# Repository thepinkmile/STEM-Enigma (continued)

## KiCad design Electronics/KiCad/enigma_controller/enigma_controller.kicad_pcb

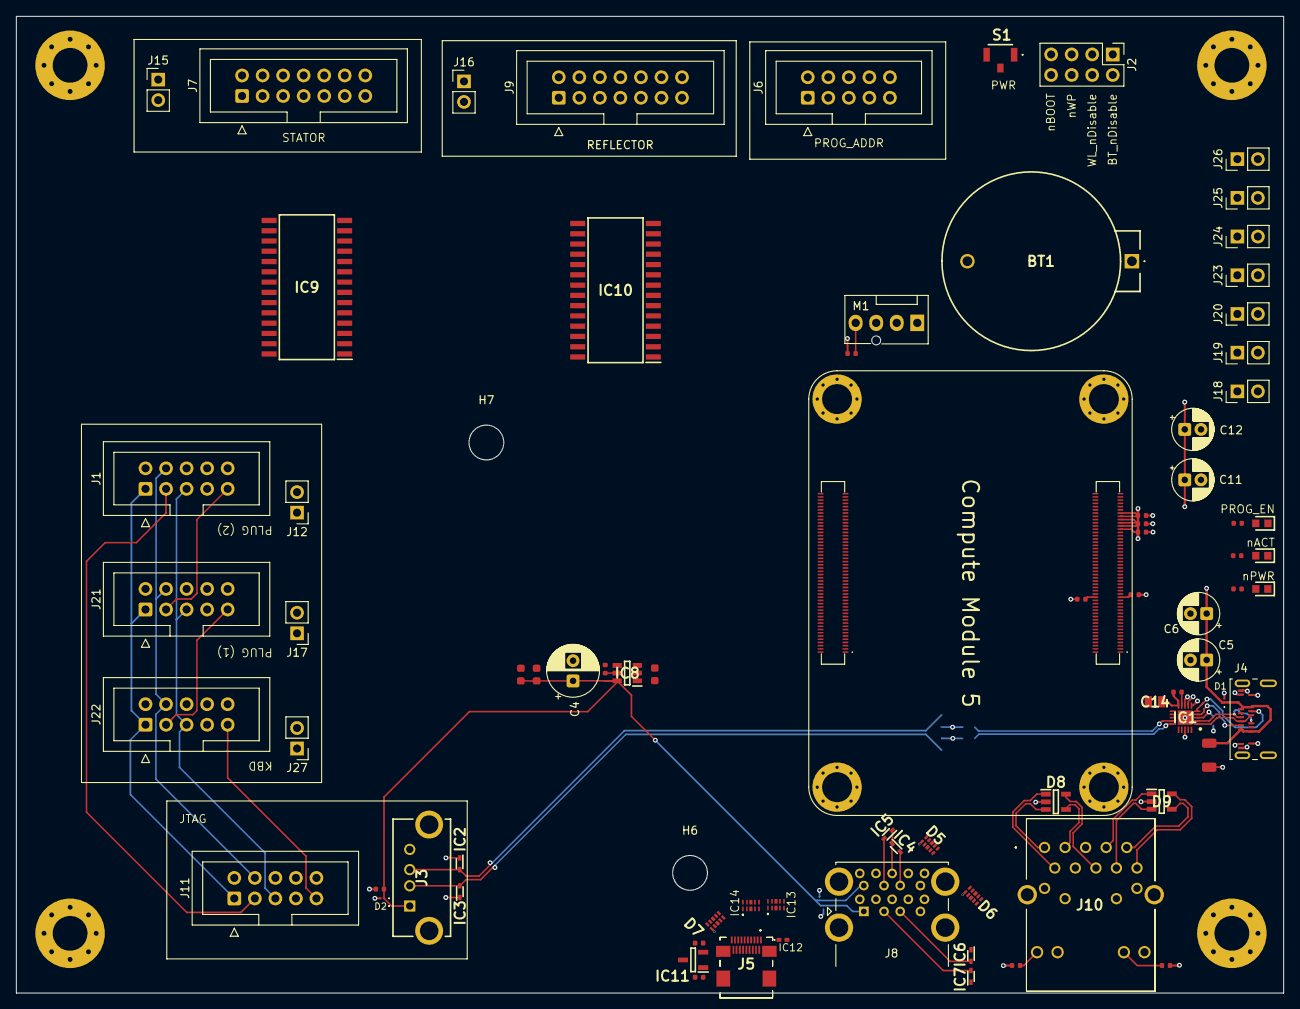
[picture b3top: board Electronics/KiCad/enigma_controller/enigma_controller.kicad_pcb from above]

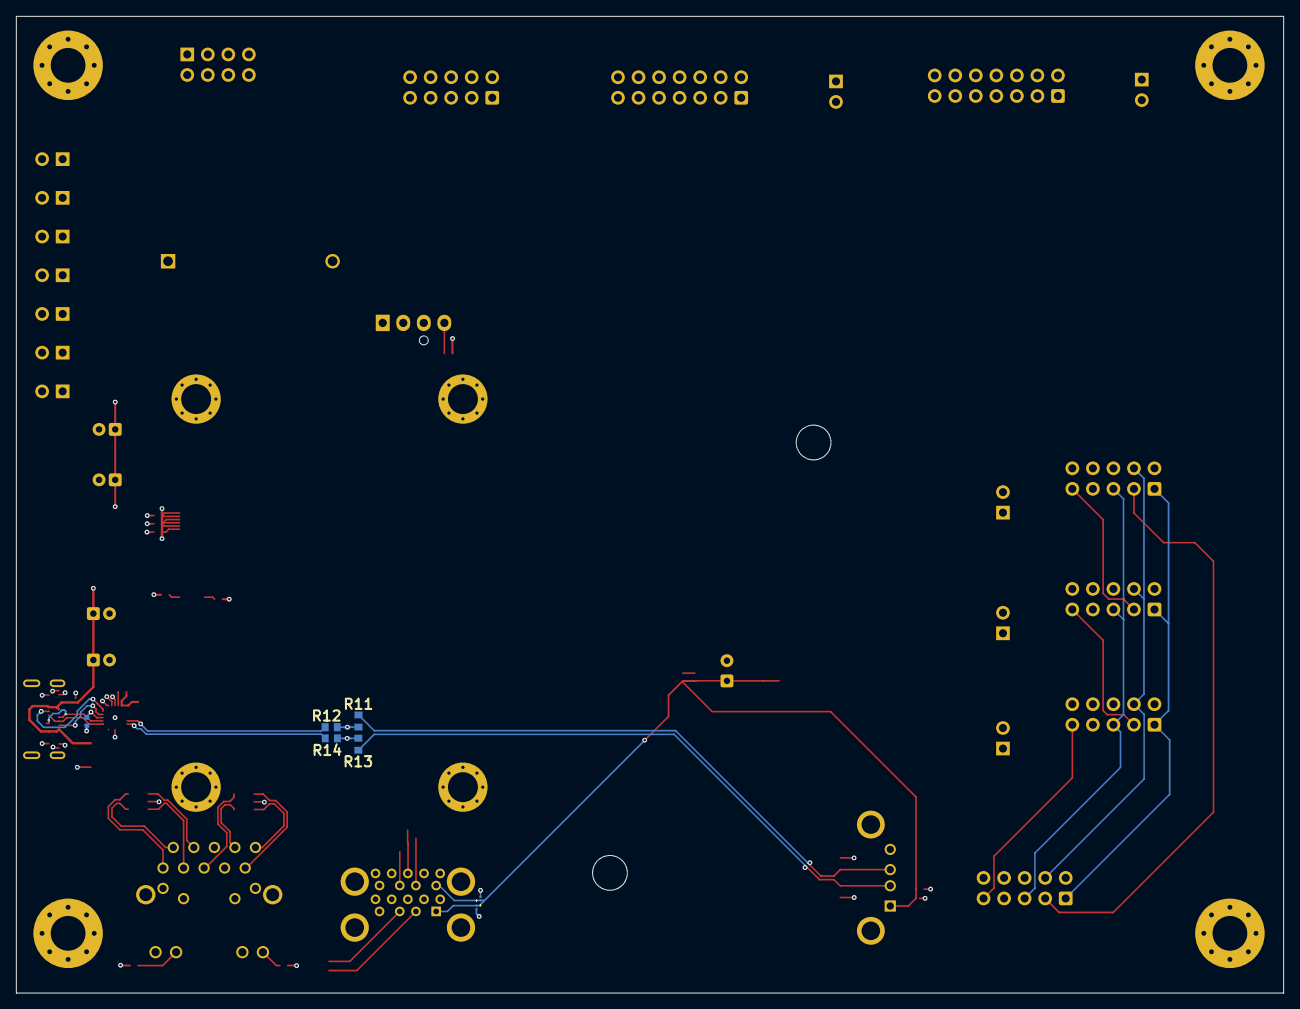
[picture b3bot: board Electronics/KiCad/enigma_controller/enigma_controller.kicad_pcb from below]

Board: 6 copper layers, 156.7 x 120.8 mm, 92 parts (7 on the bottom side), 135 nets.

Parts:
BT1: BS-02-A1AJ006; BS02A1AJ006
C1, C2, C7, C8, C9, C15, C16: 100nF; C_0402
C3, C18, C19: 10uF; C_0603
C4: 100uF_25V; CP_Radial_D6.3mm_P2.50mm
C5, C6, C11, C12: 4.7uF 50V; CP_Radial_D5.0mm_P2.00mm
C13: 2.2uF; C_1206
C14: CL21B105KAFNNNG; CAPC2012X135N
D1, D2, D3, D4: ESD441DPLR
D5, D6: TPD4E02B04DQAR; DQA(R-PUSON-N10)
D7: TPD4E05U06DQAR; DQA(R-PUSON-N10)
D8, D9: ESDS314DBVR; SOT95P280X145-5N
H1: RaspberryPi-CM5-Carrier-Tall-Pad-Via-Standoff
H2, H3, H4, H5: MountingHole_Pad; MountingHole_4.3mm_M4_Pad_Via
H6, H7: MountingHole; MountingHole_4.3mm_M4
IC1: TPD8S300ARUKR; QFN40P300X300X80-21N-D
IC2, IC3, IC4, IC5, IC6, IC7: ESD321DYAR; SODFL1608X77N
IC8: AP22653W6-7; SOT95P280X145-6N
IC9, IC10: MCP23017-E_SO; SOIC127P1030X265-28N
IC11: RT9742SNGV; SOT95P279X130-3N
IC12: TPD1E05U06DPYT
IC13, IC14: ESD224DQAR
J1, J6, J11, J21, J22: Conn_02x05_Odd_Even; IDC-Header_2x05_P2.54mm_Vertical
J2: Conn_02x04_Odd_Even; PinHeader_2x04_P2.54mm_Vertical
J3: USB1040-GF-L-B; USB1040GFLB
J4: USB_C_Receptacle_USB2.0_16P; USB_C_Receptacle_Amphenol_124019772112A
J5: 46765-0301; 467650301
J7, J9: Conn_02x07_Odd_Even; IDC-Header_2x07_P2.54mm_Vertical
J8: USB3_A_Stacked; USB3_A_Molex_48406-0001_Horizontal_Stacked
J10: A70-112-331N126; A70112331N126
J12, J15, J16, J17, J18, J19, J20, J23, J24, J25, J26, J27: Conn_01x02; PinHeader_1x02_P2.54mm_Vertical
LED1, LED2, LED87: KT-0603R; LEDC1608X70N
M1: Fan_4pin; FanPinHeader_1x04_P2.54mm_Vertical
R1, R2, R3, R4: 470Ω; R_0402
R5: 100kΩ; R_0402
R6, R7: 2.2kΩ; R_0402
R8: 10kΩ; R_0402
R9: 15kΩ; R_0402
R10: 1kΩ; R_0402
R11, R12, R13, R14: RCA06030000ZSEA; RESC1608X50N
S1: B3U-1100PM; B3U1100PM

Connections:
+3V3: C11.1, C12.1, C14.2, C15.1, H1.78 (GPIO_VREF), H1.84 (CM5_3.3V_(Output)), H1.86 (CM5_3.3V_(Output)), IC1.10 (VPWR), IC9.9 (VDD), IC10.9 (VDD), IC10.15 (A0), J12.1, J15.1, J16.1, J17.1, J18.1, J19.1, J20.1, J23.1, J24.1, J25.1, J26.1, J27.1, R1.2, R2.2, R3.2, R4.2, R5.1, R6.2, R7.1, R8.1
+5V: C1.1, C2.1, C5.1, C6.1, C7.1, C9.1, C13.1, C18.1, D1.1, H1.77 (+5V_(Input)), H1.79 (+5V_(Input)), H1.81 (+5V_(Input)), H1.83 (+5V_(Input)), H1.85 (+5V_(Input)), H1.87 (+5V_(Input)), IC8.1 (IN), IC11.1 (VIN), J4.A4 (VBUS), J4.A9 (VBUS), J4.B4 (VBUS), J4.B9 (VBUS), M1.2 (+)
/BT_nDisable: H1.91 (BT_nDisable), J2.2
/C_CC1: IC1.4 (C_CC1), J4.A5 (CC1)
/C_CC2: IC1.5 (C_CC2), J4.B5 (CC2)
/C_D+: IC1.1 (C_SBU1), J4.A6 (D+), J4.B6 (D+)
/C_D-: IC1.2 (C_SBU2), J4.A7 (D-), J4.B7 (D-)
/EEPROM_nWP: H1.20 (EEPROM_nWP), J2.6
/ETH_LED_nAct: H1.15 (Ethernet_nLED3), J10.P16 (GREEN_CATHODE)
/ETH_LED_nSpeed: H1.17 (Ethernet_nLED2), J10.P18 (YELLOW_CATHODE)
/ETH_PAIR0_N: D8.1 (I/O1), H1.10 (Ethernet_Pair0_N), J10.P2
/ETH_PAIR0_P: D8.3 (I/O2), H1.12 (Ethernet_Pair0_P), J10.P1
/ETH_PAIR1_N: D8.5 (I/O4), H1.6 (Ethernet_Pair1_N), J10.P6
/ETH_PAIR1_P: D8.4 (I/O3), H1.4 (Ethernet_Pair1_P), J10.P3
/ETH_PAIR2_N: D9.3 (I/O2), H1.9 (Ethernet_Pair2_N), J10.P8
/ETH_PAIR2_P: D9.1 (I/O1), H1.11 (Ethernet_Pair2_P), J10.P7
/ETH_PAIR3_N: D9.5 (I/O4), H1.5 (Ethernet_Pair3_N), J10.P10
/ETH_PAIR3_P: D9.4 (I/O3), H1.3 (Ethernet_Pair3_P), J10.P9
/EXP1_INT_A: H1.54 (GPIO4), IC9.20 (INTA)
/EXP1_INT_B: H1.50 (GPIO17), IC9.19 (INTB)
/EXP1_nRST: H1.58 (GPIO2), IC9.18 (~RESET)
/EXP2_INT_A: H1.48 (GPIO27), IC10.20 (INTA)
/EXP2_INT_B: H1.46 (GPIO22), IC10.19 (INTB)
/EXP2_nRST: H1.56 (GPIO3), IC10.18 (~RESET)
/FLASH_D+: IC1.14 (SBU2), R12.2
/FLASH_D-: IC1.15 (SBU1), R14.2
/Fan_PWM: H1.19 (Fan_PWM), M1.4 (PWM), R8.2
/Fan_Tacho: H1.16 (Fan_Tacho), M1.3 (Tacho)
/I2C_SCL: H1.80 (SCL0), IC9.12 (SCL), IC10.12 (SCL)
/I2C_SDA: H1.82 (SDA0), IC9.13 (SDA), IC10.13 (SDA)
/JTAG_USB_N: IC3.2 (IO), J3.2, R13.2
/JTAG_USB_P: IC2.2 (IO), J3.3, R11.2
/LED_nACT: H1.21 (LED_nACT), LED1.1
/LED_nPWR: H1.95 (PI_LED_nPWR), LED2.1
/MAP_ADDR_1: H1.44 (GPIO10), J6.1
/MAP_ADDR_2: H1.38 (GPIO11), J6.2
/MAP_ADDR_3: H1.31 (GPIO12), J6.3
/MAP_ADDR_4: H1.28 (GPIO13), J6.4
/MAP_ADDR_5: H1.55 (GPIO14), J6.5
/MAP_ADDR_6: H1.51 (GPIO15), J6.6
/MAP_ADDR_7: H1.29 (GPIO16), J6.7
/PD_CC1: H1.94 (CC1), IC1.12 (CC1)
/PD_CC2: H1.96 (CC2), IC1.11 (CC2)
/PROG_EN: H1.25 (GPIO21), J6.8, R10.2
/PROG_nWE_A: H1.26 (GPIO19), J6.9
/PROG_nWE_B: H1.27 (GPIO20), J6.10
/SHIELD: H2.1, H3.1, H4.1, H5.1, J3.5 (MH1), J3.6 (MH2), J4.S1 (SHIELD), J5.4 (TMDS_DATA2_SHIELD), J5.7 (TMDS_DATA1_SHIELD), J5.10 (TMDS_DATA0_SHIELD), J5.13 (TMDS_CLOCK_SHIELD), J5.MP1, J5.MP2, J5.MP3, J5.MP4, J8.19 (SHIELD), J10.MH1, J10.MH2
/TCK: J1.1, J11.1, J21.1, J22.1
/TDI: J11.9, J22.9
/TDO: J1.3, J11.3
/TDX1: J21.9, J22.3
/TDX2: J1.9, J21.3
/TMS: J1.5, J11.5, J21.5, J22.5
/USB_DN: H1.103 (USB_N), R13.1, R14.1
/USB_DP: H1.105 (USB_P), R11.1, R12.1
/VBUS: C3.1, C4.1, C16.2, C19.1, D2.1, D3.1, D4.1, IC8.6 (OUT), J3.1, J8.1 (VBUS1), J8.10 (VBUS2)
/VCC_JTAG: J1.4, J11.4, J21.4, J22.4
/WL_nDisable: H1.89 (WL_nDisable), J2.4
/enigma_controller_HS/HDMI0_CEC: D7.4 (D2+), H1.151 (HDMI0_CEC), J5.15 (CEC)
/enigma_controller_HS/HDMI0_CLK_N: H1.190 (HDMI0_CLK_N), IC14.10 (IO1_S)
/enigma_controller_HS/HDMI0_CLK_P: H1.188 (HDMI0_CLK_P), IC14.9 (IO2_S)
/enigma_controller_HS/HDMI0_HOT_PLUG: H1.153 (HDMI0_HOTPLUG), IC12.1 (I/O), J5.1 (HOT_PLUG_DETECT)
/enigma_controller_HS/HDMI0_SCL: D7.2 (D1-), H1.200 (HDMI0_SCL), J5.17 (SCL)
/enigma_controller_HS/HDMI0_SDA: D7.1 (D1+), H1.199 (HDMI0_SDA), J5.18 (SDA)
/enigma_controller_HS/HDMI0_TX0_N: H1.184 (HDMI0_TX0_N), IC14.7 (IO3_S)
/enigma_controller_HS/HDMI0_TX0_P: H1.182 (HDMI0_TX0_P), IC14.6 (IO4_S)
/enigma_controller_HS/HDMI0_TX1_N: H1.178 (HDMI0_TX1_N), IC13.10 (IO1_S)
/enigma_controller_HS/HDMI0_TX1_P: H1.176 (HDMI0_TX1_P), IC13.9 (IO2_S)
/enigma_controller_HS/HDMI0_TX2_N: H1.172 (HDMI0_TX2_N), IC13.7 (IO3_S)
/enigma_controller_HS/HDMI0_TX2_P: H1.170 (HDMI0_TX2_P), IC13.6 (IO4_S)
/enigma_controller_HS/HDMI0_UTIL: D7.5 (D2-), J5.2 (UTILITY)
/enigma_controller_HS/HDMI_5V: C8.1, IC11.2 (VOUT), J5.19 (+5V_POWER)
/enigma_controller_HS/TMDS_CLK+: IC14.2 (IO2_C), J5.12 (TMDS_CLOCK+)
/enigma_controller_HS/TMDS_CLK-: IC14.1 (IO1_C), J5.14 (TMDS_CLOCK-)
/enigma_controller_HS/TMDS_DATA0+: IC14.5 (IO4_C), J5.9 (TMDS_DATA0+)
/enigma_controller_HS/TMDS_DATA0-: IC14.4 (IO3_C), J5.11 (TMDS_DATA0-)
/enigma_controller_HS/TMDS_DATA1+: IC13.2 (IO2_C), J5.6 (TMDS_DATA1+)
/enigma_controller_HS/TMDS_DATA1-: IC13.1 (IO1_C), J5.8 (TMDS_DATA1-)
/enigma_controller_HS/TMDS_DATA2+: IC13.5 (IO4_C), J5.3 (TMDS_DATA2+)
/enigma_controller_HS/TMDS_DATA2-: IC13.4 (IO3_C), J5.5 (TMDS_DATA2-)
/enigma_controller_HS/USB3_0_DM: H1.136 (USB3-0-DM), IC7.2 (IO), J8.2 (D1-)
/enigma_controller_HS/USB3_0_DP: H1.134 (USB3-0-DP), IC6.2 (IO), J8.3 (D1+)
/enigma_controller_HS/USB3_0_RX_N: D6.1 (IO1), H1.128 (USB3-0-RX_N), J8.5 (SSRX1-)
/enigma_controller_HS/USB3_0_RX_P: D6.2 (IO2), H1.130 (USB3-0-RX_P), J8.6 (SSRX1+)
/enigma_controller_HS/USB3_0_TX_N: D6.4 (IO3), H1.140 (USB3-0-TX_N), J8.8 (SSTX1-)
/enigma_controller_HS/USB3_0_TX_P: D6.5 (IO4), H1.142 (USB3-0-TX_P), J8.9 (SSTX1+)
/enigma_controller_HS/USB3_1_DM: H1.165 (USB3-1-DM), IC5.2 (IO), J8.11 (D2-)
/enigma_controller_HS/USB3_1_DP: H1.163 (USB3-1-DP), IC4.2 (IO), J8.12 (D2+)
/enigma_controller_HS/USB3_1_RX_N: D5.1 (IO1), H1.157 (USB3-1-RX_N), J8.14 (SSRX2-)
/enigma_controller_HS/USB3_1_RX_P: D5.2 (IO2), H1.159 (USB3-1-RX_P), J8.15 (SSRX2+)
/enigma_controller_HS/USB3_1_TX_N: D5.4 (IO3), H1.169 (USB3-1-TX_N), J8.17 (SSTX2-)
/enigma_controller_HS/USB3_1_TX_P: D5.5 (IO4), H1.171 (USB3-1-TX_P), J8.18 (SSTX2+)
/enigma_controller_HS/VBUS_EN: H1.111 (VBUS_EN), IC8.3 (EN)
/nRPIBOOT: H1.93 (nRPIBOOT), J2.8
/pBIN_IN_A1: IC9.1 (GPB0), J7.1
/pBIN_IN_A2: IC9.2 (GPB1), J7.3
/pBIN_IN_A3: IC9.3 (GPB2), J7.5
/pBIN_IN_A4: IC9.4 (GPB3), J7.7
/pBIN_IN_A5: IC9.5 (GPB4), J7.9
/pBIN_IN_A6: IC9.6 (GPB5), J7.11
/pBIN_IN_B1: IC10.1 (GPB0), J9.2
/pBIN_IN_B2: IC10.2 (GPB1), J9.4
/pBIN_IN_B3: IC10.3 (GPB2), J9.6
/pBIN_IN_B4: IC10.4 (GPB3), J9.8
/pBIN_IN_B5: IC10.5 (GPB4), J9.10
/pBIN_IN_B6: IC10.6 (GPB5), J9.12
/pBIN_IN_nOE_A: IC9.7 (GPB6), J7.13
/pBIN_IN_nOE_B: IC10.7 (GPB6), J9.14
/pBIN_OUT_A1: IC9.21 (GPA0), J9.1
/pBIN_OUT_A2: IC9.22 (GPA1), J9.3
/pBIN_OUT_A3: IC9.23 (GPA2), J9.5
/pBIN_OUT_A4: IC9.24 (GPA3), J9.7
/pBIN_OUT_A5: IC9.25 (GPA4), J9.9
/pBIN_OUT_A6: IC9.26 (GPA5), J9.11
/pBIN_OUT_B1: IC10.21 (GPA0), J7.2
/pBIN_OUT_B2: IC10.22 (GPA1), J7.4
/pBIN_OUT_B3: IC10.23 (GPA2), J7.6
/pBIN_OUT_B4: IC10.24 (GPA3), J7.8
/pBIN_OUT_B5: IC10.25 (GPA4), J7.10
/pBIN_OUT_B6: IC10.26 (GPA5), J7.12
/pBIN_OUT_nOE_A: IC9.27 (GPA6), J9.13
/pBIN_OUT_nOE_B: IC10.27 (GPA6), J7.14
GND: BT1.2 (-), C1.2, C2.2, C3.2, C4.2, C5.2, C6.2, C7.2, C8.2, C9.2, C11.2, C12.2, C13.2, C14.1, C16.1, C18.2, C19.2, D1.2, D2.2, D3.2, D4.2, D5.3 (GND_1), D5.8 (GND_2), D6.3 (GND_1), D6.8 (GND_2), D7.3 (GND_1), D7.8 (GND_2), D8.2 (GND), D9.2 (GND), H1.1 (GND), H1.2 (GND), H1.7 (GND), H1.8 (GND), H1.13 (GND), H1.14 (GND), H1.22 (GND), H1.23 (GND), H1.32 (GND), H1.33 (GND), H1.42 (GND), H1.43 (GND), H1.52 (GND), H1.53 (GND), H1.59 (GND), H1.60 (GND), H1.65 (GND), H1.66 (GND), H1.71 (GND), H1.74 (GND), H1.98 (GND), H1.107 (GND), H1.108 (GND), H1.113 (GND), H1.114 (GND), H1.119 (GND), H1.120 (GND), H1.125 (GND), H1.126 (GND), H1.131 (GND), H1.132 (GND), H1.137 (GND), H1.138 (GND), H1.144 (GND), H1.150 (GND), H1.155 (GND), H1.156 (GND), H1.161 (GND), H1.162 (GND), H1.167 (GND), H1.168 (GND), H1.173 (GND), H1.174 (GND), H1.179 (GND), H1.180 (GND), H1.185 (GND), H1.186 (GND), H1.191 (GND), H1.192 (GND), H1.197 (GND), H1.198 (GND), IC1.6 (RPD_G2), IC1.7 (RPD_G1), IC1.8 (GND_1), IC1.13 (GND_2), IC1.18 (GND_3), IC1.21 (EP), IC2.1 (GND), IC3.1 (GND), IC4.1 (GND), IC5.1 (GND), IC6.1 (GND), IC7.1 (GND), IC8.2 (GND), IC9.10 (VSS), IC9.15 (A0), IC9.16 (A1), IC9.17 (A2), IC10.10 (VSS), IC10.16 (A1), IC10.17 (A2), IC11.3 (GND), IC12.2 (GND), IC13.3 (GND_1), IC13.8 (GND_2), IC14.3 (GND_1), IC14.8 (GND_2), J1.2, J1.10, J2.1, J2.3, J2.5, J2.7, J3.4, J4.A1 (GND), J4.A12 (GND), J4.B1 (GND), J4.B12 (GND), J5.16 (DDC/CEC_GROUND), J8.4 (GND1), J8.7 (DRAIN1), J8.13 (GND2), J8.16 (DRAIN2), J10.P4, J10.P5, J11.2, J11.10, J12.2, J15.2, J16.2, J17.2, J18.2, J19.2, J20.2, J21.2, J21.10, J22.2, J22.10, J23.2, J24.2, J25.2, J26.2, J27.2, LED87.1, M1.1 (-), R9.2, S1.1 (COM), S1.3 (GND)
unnamed: BT1.1 (+), H1.76 (VBAT)
unnamed: H1.35 (ID_SC), R6.1
unnamed: H1.36 (ID_SD), R7.2
unnamed: H1.92 (PWR_Button), S1.2 (NO)
unnamed: C15.2, IC1.3 (VBIAS)
unnamed: IC1.9 (~FLT), R5.2
unnamed: IC8.5 (ILIM), R9.1
unnamed: J10.P15 (GREEN_ANODE), R3.1
unnamed: J10.P17 (YELLOW_ANODE), R4.1
unnamed: LED1.2, R1.1
unnamed: LED2.2, R2.1
unnamed: LED87.2, R10.1

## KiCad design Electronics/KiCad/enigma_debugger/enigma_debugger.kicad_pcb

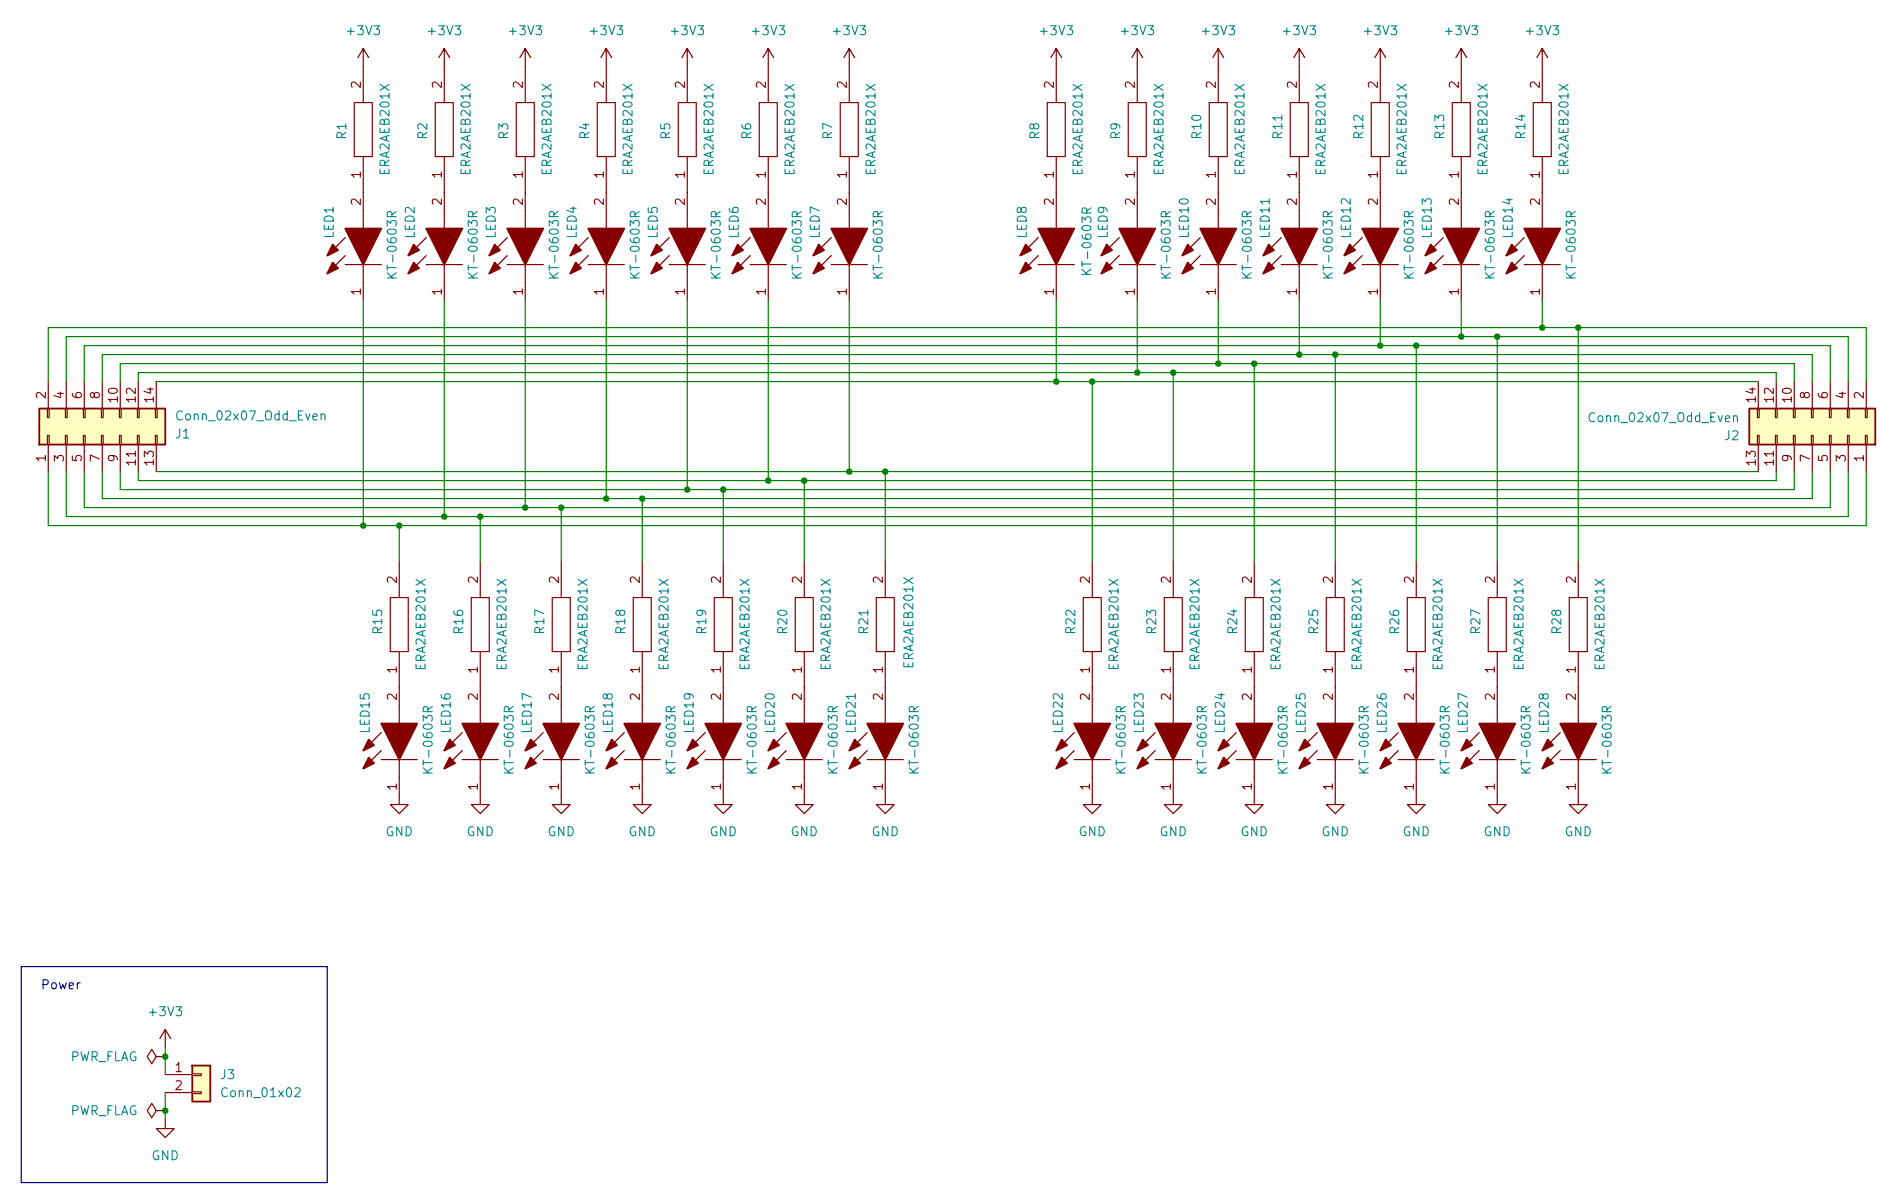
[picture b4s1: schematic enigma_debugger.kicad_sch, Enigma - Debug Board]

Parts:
J1, J2: Conn_02x07_Odd_Even; IDC-Header_2x07_P2.54mm_Vertical
J3: Conn_01x02; PinHeader_1x02_P2.54mm_Vertical
LED1, LED2, LED3, LED4, LED5, LED6, LED7, LED8, LED9, LED10, LED11, LED12, LED13, LED14, LED15, LED16, LED17, LED18, LED19, LED20, LED21, LED22, LED23, LED24, LED25, LED26, LED27, LED28: KT-0603R; LEDC1608X70N; Manufacturer_Part_Number KT-0603R
R1, R2, R3, R4, R5, R6, R7, R8, R9, R10, R11, R12, R13, R14, R15, R16, R17, R18, R19, R20, R21, R22, R23, R24, R25, R26, R27, R28: ERA2AEB201X; ERA2AED122X; Manufacturer_Part_Number ERA2AEB201X

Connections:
+3V3: J3.1, R1.2, R2.2, R3.2, R4.2, R5.2, R6.2, R7.2, R8.2, R9.2, R10.2, R11.2, R12.2, R13.2, R14.2
GND: J3.2, LED15.1, LED16.1, LED17.1, LED18.1, LED19.1, LED20.1, LED21.1, LED22.1, LED23.1, LED24.1, LED25.1, LED26.1, LED27.1, LED28.1
unnamed: J1.1, J2.1, LED1.1, R15.2
unnamed: J1.2, J2.2, LED14.1, R28.2
unnamed: J1.3, J2.3, LED2.1, R16.2
unnamed: J1.4, J2.4, LED13.1, R27.2
unnamed: J1.5, J2.5, LED3.1, R17.2
unnamed: J1.6, J2.6, LED12.1, R26.2
unnamed: J1.7, J2.7, LED4.1, R18.2
unnamed: J1.8, J2.8, LED11.1, R25.2
unnamed: J1.9, J2.9, LED5.1, R19.2
unnamed: J1.10, J2.10, LED10.1, R24.2
unnamed: J1.11, J2.11, LED6.1, R20.2
unnamed: J1.12, J2.12, LED9.1, R23.2
unnamed: J1.13, J2.13, LED7.1, R21.2
unnamed: J1.14, J2.14, LED8.1, R22.2
unnamed: LED1.2, R1.1
unnamed: LED2.2, R2.1
unnamed: LED3.2, R3.1
unnamed: LED4.2, R4.1
unnamed: LED5.2, R5.1
unnamed: LED6.2, R6.1
unnamed: LED7.2, R7.1
unnamed: LED8.2, R8.1
unnamed: LED9.2, R9.1
unnamed: LED10.2, R10.1
unnamed: LED11.2, R11.1
unnamed: LED12.2, R12.1
unnamed: LED13.2, R13.1
unnamed: LED14.2, R14.1
unnamed: LED15.2, R15.1
unnamed: LED16.2, R16.1
unnamed: LED17.2, R17.1
unnamed: LED18.2, R18.1
unnamed: LED19.2, R19.1
unnamed: LED20.2, R20.1
unnamed: LED21.2, R21.1
unnamed: LED22.2, R22.1
unnamed: LED23.2, R23.1
unnamed: LED24.2, R24.1
unnamed: LED25.2, R25.1
unnamed: LED26.2, R26.1
unnamed: LED27.2, R27.1
unnamed: LED28.2, R28.1

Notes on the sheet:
Power

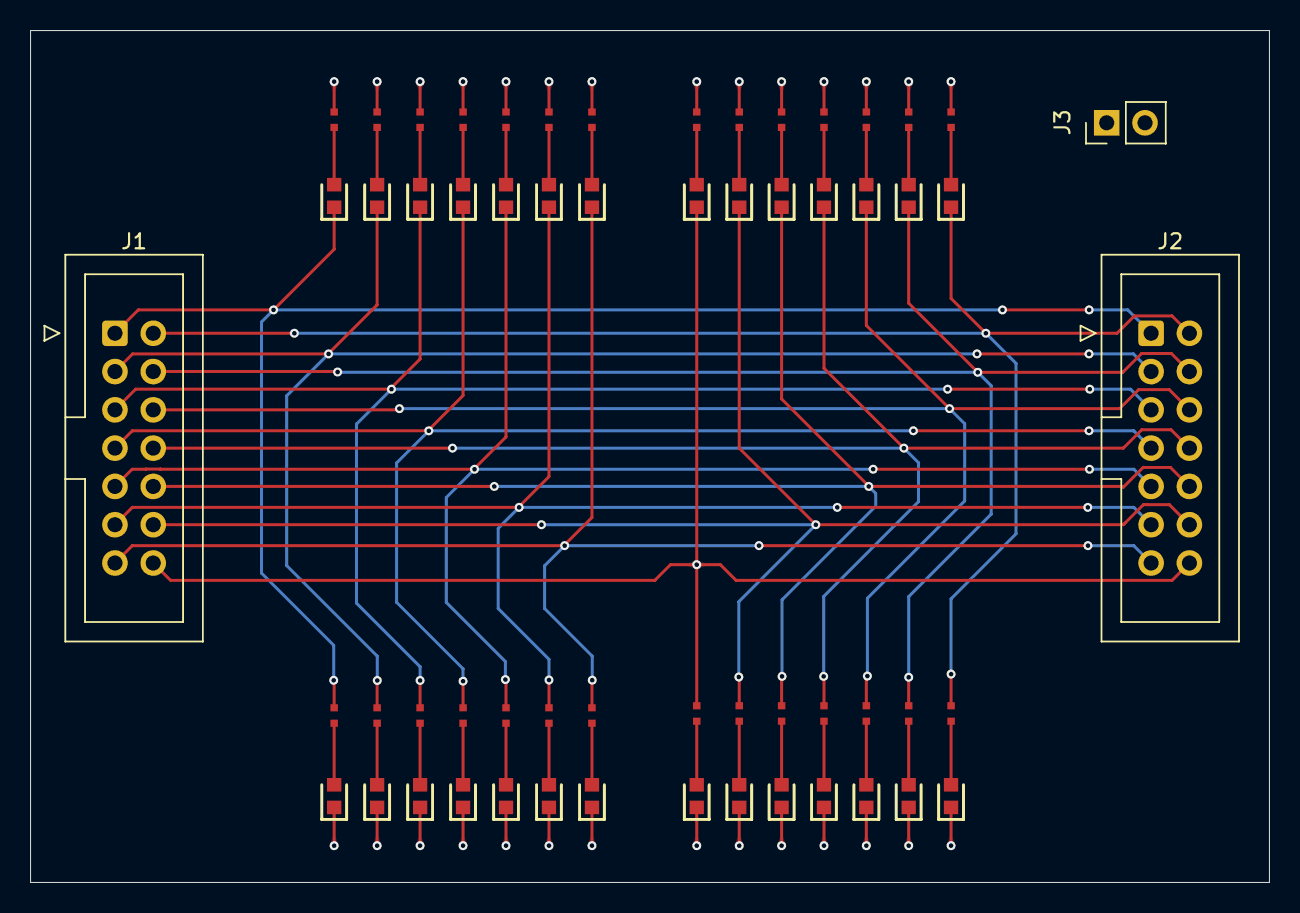
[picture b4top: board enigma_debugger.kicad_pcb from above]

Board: 4 copper layers, 82.2 x 56.5 mm, 59 parts (0 on the bottom side), 44 nets.

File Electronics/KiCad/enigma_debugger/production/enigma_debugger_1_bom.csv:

Designator,Footprint,Quantity,Value,LCSC Part #
"J1, J2",IDC-Header_2x07_P2.54mm_Vertical,2,Conn_02x07_Odd_Even,C11215
J3,PinHeader_1x02_P2.54mm_Vertical,1,Conn_01x02,C32713268
"LED1, LED10, LED11, LED12, LED13, LED14, LED15, LED16, LED17, LED18, LED19, LED2, LED20, LED21, LED22, LED23, LED24, LED25, LED26, LED27, LED28, LED3, LED4, LED5, LED6, LED7, LED8, LED9",LEDC1608X70N,28,KT-0603R,C2286
"R1, R10, R11, R12, R13, R14, R15, R16, R17, R18, R19, R2, R20, R21, R22, R23, R24, R25, R26, R27, R28, R3, R4, R5, R6, R7, R8, R9",ERA2AED122X,28,ERA2AEB201X,C445582

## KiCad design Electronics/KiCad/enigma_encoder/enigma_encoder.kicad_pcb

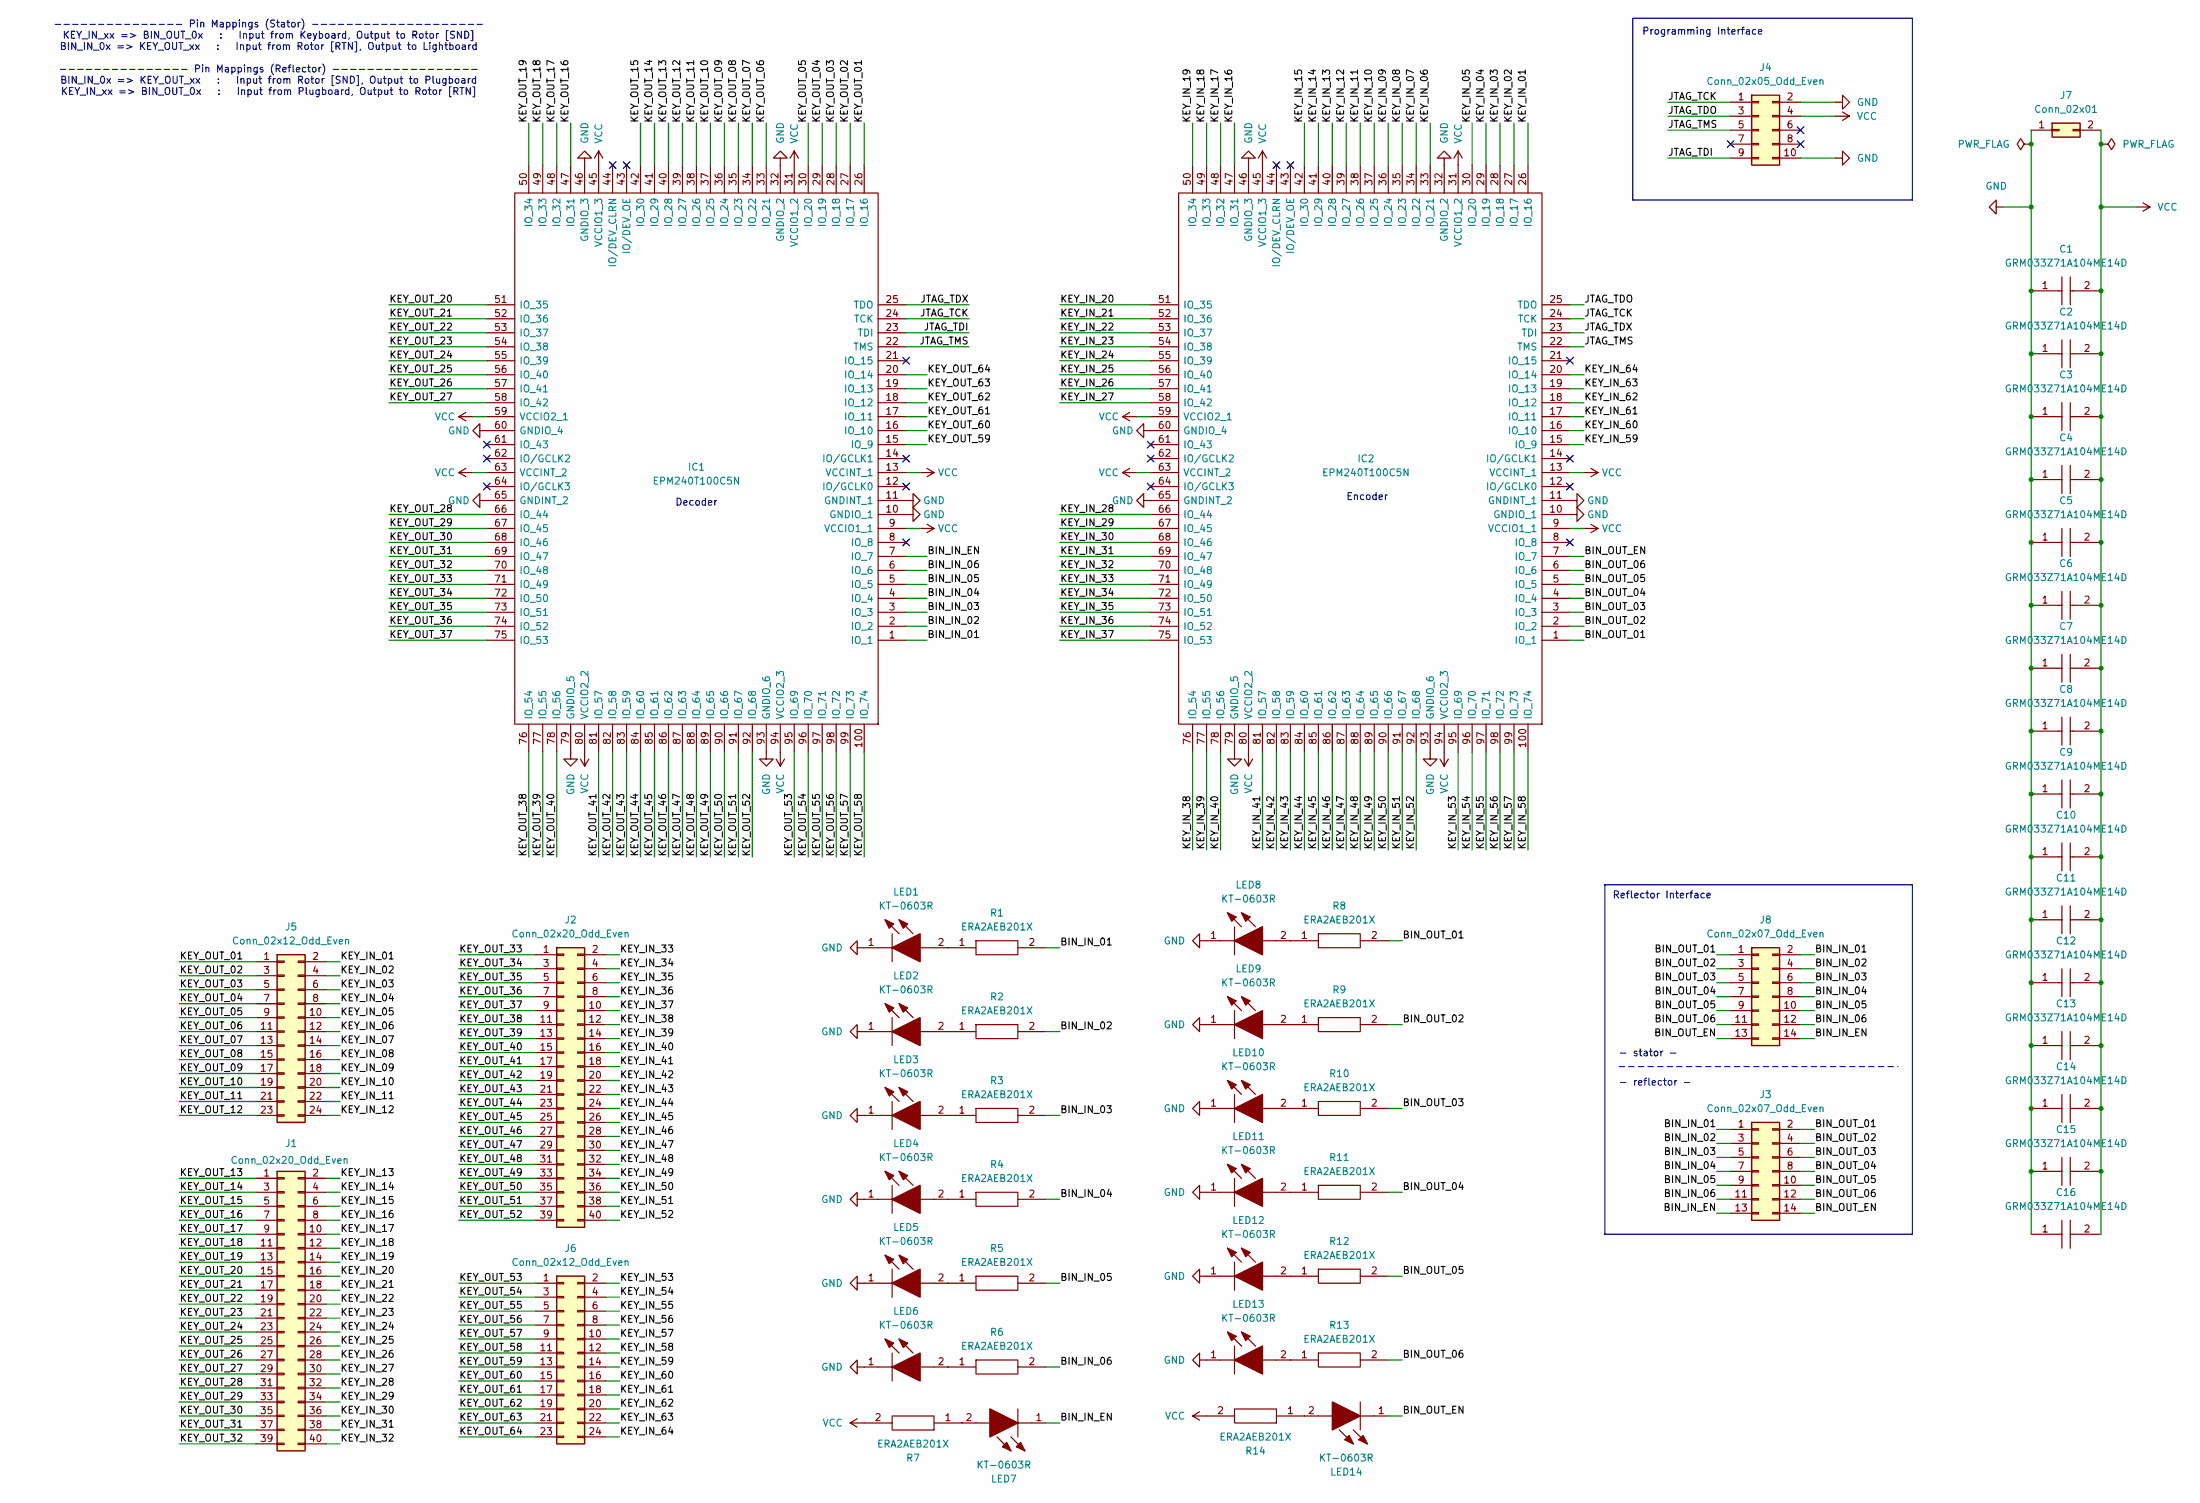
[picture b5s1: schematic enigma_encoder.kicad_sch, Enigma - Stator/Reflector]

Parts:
C1, C2, C3, C4, C5, C6, C7, C8, C9, C10, C11, C12, C13, C14, C15, C16: GRM033Z71A104ME14D; GRM033D70J224ME01D; Manufacturer_Part_Number GRM033Z71A104ME14D; Mouser Part Number 81-GRM033Z71A104ME4D
IC1, IC2: EPM240T100C5N; QFP50P1600X1600X120-100N; Manufacturer_Part_Number EPM240T100C5N; Mouser Part Number 989-EPM240T100C5N
J1, J2: Conn_02x20_Odd_Even; IDC-Header_2x20_P2.54mm_Vertical
J3, J8: Conn_02x07_Odd_Even; IDC-Header_2x07_P2.54mm_Vertical
J4: Conn_02x05_Odd_Even; IDC-Header_2x05_P2.54mm_Vertical
J5, J6: Conn_02x12_Odd_Even; IDC-Header_2x12_P2.54mm_Vertical
J7: Conn_02x01; PinHeader_2x01_P2.54mm_Vertical
LED1, LED2, LED3, LED4, LED5, LED6, LED7, LED8, LED9, LED10, LED11, LED12, LED13, LED14: KT-0603R; LEDC1608X70N; Manufacturer_Part_Number KT-0603R
R1, R2, R3, R4, R5, R6, R7, R8, R9, R10, R11, R12, R13, R14: ERA2AEB201X; ERA2AED122X; Manufacturer_Part_Number ERA2AEB201X

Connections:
/BIN_IN_01: IC1.1 (IO_1), J3.1, J8.2, R1.2
/BIN_IN_02: IC1.2 (IO_2), J3.3, J8.4, R2.2
/BIN_IN_03: IC1.3 (IO_3), J3.5, J8.6, R3.2
/BIN_IN_04: IC1.4 (IO_4), J3.7, J8.8, R4.2
/BIN_IN_05: IC1.5 (IO_5), J3.9, J8.10, R5.2
/BIN_IN_06: IC1.6 (IO_6), J3.11, J8.12, R6.2
/BIN_OUT_01: IC2.1 (IO_1), J3.2, J8.1, R8.2
/BIN_OUT_02: IC2.2 (IO_2), J3.4, J8.3, R9.2
/BIN_OUT_03: IC2.3 (IO_3), J3.6, J8.5, R10.2
/BIN_OUT_04: IC2.4 (IO_4), J3.8, J8.7, R11.2
/BIN_OUT_05: IC2.5 (IO_5), J3.10, J8.9, R12.2
/BIN_OUT_06: IC2.6 (IO_6), J3.12, J8.11, R13.2
/JTAG_TCK: IC1.24 (TCK), IC2.24 (TCK), J4.1
/JTAG_TDI: IC1.23 (TDI), J4.9
/JTAG_TDO: IC2.25 (TDO), J4.3
/JTAG_TDX: IC1.25 (TDO), IC2.23 (TDI)
/JTAG_TMS: IC1.22 (TMS), IC2.22 (TMS), J4.5
/KEY_IN_01: IC2.26 (IO_16), J5.2
/KEY_IN_02: IC2.27 (IO_17), J5.4
/KEY_IN_03: IC2.28 (IO_18), J5.6
/KEY_IN_04: IC2.29 (IO_19), J5.8
/KEY_IN_05: IC2.30 (IO_20), J5.10
/KEY_IN_06: IC2.33 (IO_21), J5.12
/KEY_IN_07: IC2.34 (IO_22), J5.14
/KEY_IN_08: IC2.35 (IO_23), J5.16
/KEY_IN_09: IC2.36 (IO_24), J5.18
/KEY_IN_10: IC2.37 (IO_25), J5.20
/KEY_IN_11: IC2.38 (IO_26), J5.22
/KEY_IN_12: IC2.39 (IO_27), J5.24
/KEY_IN_13: IC2.40 (IO_28), J1.2
/KEY_IN_14: IC2.41 (IO_29), J1.4
/KEY_IN_15: IC2.42 (IO_30), J1.6
/KEY_IN_16: IC2.47 (IO_31), J1.8
/KEY_IN_17: IC2.48 (IO_32), J1.10
/KEY_IN_18: IC2.49 (IO_33), J1.12
/KEY_IN_19: IC2.50 (IO_34), J1.14
/KEY_IN_20: IC2.51 (IO_35), J1.16
/KEY_IN_21: IC2.52 (IO_36), J1.18
/KEY_IN_22: IC2.53 (IO_37), J1.20
/KEY_IN_23: IC2.54 (IO_38), J1.22
/KEY_IN_24: IC2.55 (IO_39), J1.24
/KEY_IN_25: IC2.56 (IO_40), J1.26
/KEY_IN_26: IC2.57 (IO_41), J1.28
/KEY_IN_27: IC2.58 (IO_42), J1.30
/KEY_IN_28: IC2.66 (IO_44), J1.32
/KEY_IN_29: IC2.67 (IO_45), J1.34
/KEY_IN_30: IC2.68 (IO_46), J1.36
/KEY_IN_31: IC2.69 (IO_47), J1.38
/KEY_IN_32: IC2.70 (IO_48), J1.40
/KEY_IN_33: IC2.71 (IO_49), J2.2
/KEY_IN_34: IC2.72 (IO_50), J2.4
/KEY_IN_35: IC2.73 (IO_51), J2.6
/KEY_IN_36: IC2.74 (IO_52), J2.8
/KEY_IN_37: IC2.75 (IO_53), J2.10
/KEY_IN_38: IC2.76 (IO_54), J2.12
/KEY_IN_39: IC2.77 (IO_55), J2.14
/KEY_IN_40: IC2.78 (IO_56), J2.16
/KEY_IN_41: IC2.81 (IO_57), J2.18
/KEY_IN_42: IC2.82 (IO_58), J2.20
/KEY_IN_43: IC2.83 (IO_59), J2.22
/KEY_IN_44: IC2.84 (IO_60), J2.24
/KEY_IN_45: IC2.85 (IO_61), J2.26
/KEY_IN_46: IC2.86 (IO_62), J2.28
/KEY_IN_47: IC2.87 (IO_63), J2.30
/KEY_IN_48: IC2.88 (IO_64), J2.32
/KEY_IN_49: IC2.89 (IO_65), J2.34
/KEY_IN_50: IC2.90 (IO_66), J2.36
/KEY_IN_51: IC2.91 (IO_67), J2.38
/KEY_IN_52: IC2.92 (IO_68), J2.40
/KEY_IN_53: IC2.95 (IO_69), J6.2
/KEY_IN_54: IC2.96 (IO_70), J6.4
/KEY_IN_55: IC2.97 (IO_71), J6.6
/KEY_IN_56: IC2.98 (IO_72), J6.8
/KEY_IN_57: IC2.99 (IO_73), J6.10
/KEY_IN_58: IC2.100 (IO_74), J6.12
/KEY_IN_59: IC2.15 (IO_9), J6.14
/KEY_IN_60: IC2.16 (IO_10), J6.16
/KEY_IN_61: IC2.17 (IO_11), J6.18
/KEY_IN_62: IC2.18 (IO_12), J6.20
/KEY_IN_63: IC2.19 (IO_13), J6.22
/KEY_IN_64: IC2.20 (IO_14), J6.24
/KEY_OUT_01: IC1.26 (IO_16), J5.1
/KEY_OUT_02: IC1.27 (IO_17), J5.3
/KEY_OUT_03: IC1.28 (IO_18), J5.5
/KEY_OUT_04: IC1.29 (IO_19), J5.7
/KEY_OUT_05: IC1.30 (IO_20), J5.9
/KEY_OUT_06: IC1.33 (IO_21), J5.11
/KEY_OUT_07: IC1.34 (IO_22), J5.13
/KEY_OUT_08: IC1.35 (IO_23), J5.15
/KEY_OUT_09: IC1.36 (IO_24), J5.17
/KEY_OUT_10: IC1.37 (IO_25), J5.19
/KEY_OUT_11: IC1.38 (IO_26), J5.21
/KEY_OUT_12: IC1.39 (IO_27), J5.23
/KEY_OUT_13: IC1.40 (IO_28), J1.1
/KEY_OUT_14: IC1.41 (IO_29), J1.3
/KEY_OUT_15: IC1.42 (IO_30), J1.5
/KEY_OUT_16: IC1.47 (IO_31), J1.7
/KEY_OUT_17: IC1.48 (IO_32), J1.9
/KEY_OUT_18: IC1.49 (IO_33), J1.11
/KEY_OUT_19: IC1.50 (IO_34), J1.13
/KEY_OUT_20: IC1.51 (IO_35), J1.15
/KEY_OUT_21: IC1.52 (IO_36), J1.17
/KEY_OUT_22: IC1.53 (IO_37), J1.19
/KEY_OUT_23: IC1.54 (IO_38), J1.21
/KEY_OUT_24: IC1.55 (IO_39), J1.23
/KEY_OUT_25: IC1.56 (IO_40), J1.25
/KEY_OUT_26: IC1.57 (IO_41), J1.27
/KEY_OUT_27: IC1.58 (IO_42), J1.29
/KEY_OUT_28: IC1.66 (IO_44), J1.31
/KEY_OUT_29: IC1.67 (IO_45), J1.33
/KEY_OUT_30: IC1.68 (IO_46), J1.35
/KEY_OUT_31: IC1.69 (IO_47), J1.37
/KEY_OUT_32: IC1.70 (IO_48), J1.39
/KEY_OUT_33: IC1.71 (IO_49), J2.1
/KEY_OUT_34: IC1.72 (IO_50), J2.3
/KEY_OUT_35: IC1.73 (IO_51), J2.5
/KEY_OUT_36: IC1.74 (IO_52), J2.7
/KEY_OUT_37: IC1.75 (IO_53), J2.9
/KEY_OUT_38: IC1.76 (IO_54), J2.11
/KEY_OUT_39: IC1.77 (IO_55), J2.13
/KEY_OUT_40: IC1.78 (IO_56), J2.15
/KEY_OUT_41: IC1.81 (IO_57), J2.17
/KEY_OUT_42: IC1.82 (IO_58), J2.19
/KEY_OUT_43: IC1.83 (IO_59), J2.21
/KEY_OUT_44: IC1.84 (IO_60), J2.23
/KEY_OUT_45: IC1.85 (IO_61), J2.25
/KEY_OUT_46: IC1.86 (IO_62), J2.27
/KEY_OUT_47: IC1.87 (IO_63), J2.29
/KEY_OUT_48: IC1.88 (IO_64), J2.31
/KEY_OUT_49: IC1.89 (IO_65), J2.33
/KEY_OUT_50: IC1.90 (IO_66), J2.35
/KEY_OUT_51: IC1.91 (IO_67), J2.37
/KEY_OUT_52: IC1.92 (IO_68), J2.39
/KEY_OUT_53: IC1.95 (IO_69), J6.1
/KEY_OUT_54: IC1.96 (IO_70), J6.3
/KEY_OUT_55: IC1.97 (IO_71), J6.5
/KEY_OUT_56: IC1.98 (IO_72), J6.7
/KEY_OUT_57: IC1.99 (IO_73), J6.9
/KEY_OUT_58: IC1.100 (IO_74), J6.11
/KEY_OUT_59: IC1.15 (IO_9), J6.13
/KEY_OUT_60: IC1.16 (IO_10), J6.15
/KEY_OUT_61: IC1.17 (IO_11), J6.17
/KEY_OUT_62: IC1.18 (IO_12), J6.19
/KEY_OUT_63: IC1.19 (IO_13), J6.21
/KEY_OUT_64: IC1.20 (IO_14), J6.23
unnamed: LED1.2, R1.1
unnamed: LED2.2, R2.1
unnamed: LED3.2, R3.1
unnamed: LED4.2, R4.1
unnamed: LED5.2, R5.1
unnamed: LED6.2, R6.1
unnamed: LED7.2, R7.1
unnamed: LED8.2, R8.1
unnamed: LED9.2, R9.1
unnamed: LED10.2, R10.1
unnamed: LED11.2, R11.1
unnamed: LED12.2, R12.1
unnamed: LED13.2, R13.1
unnamed: LED14.2, R14.1

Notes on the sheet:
- stator -
- reflector -
Reflector Interface
Encoder
Decoder
--------------- Pin Mappings (Stator) -------------------- KEY_IN_xx => BIN_OUT_0x : Input from Keyboard, Output to Rotor [SND] BIN_IN_0x => KEY_OUT_xx : Input from Rotor [RTN], Output to Lightboard --------------- Pin Mappings (Reflector) ----------------- BIN_IN_0x => KEY_OUT_xx : Input from Roto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
Programming Interface

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
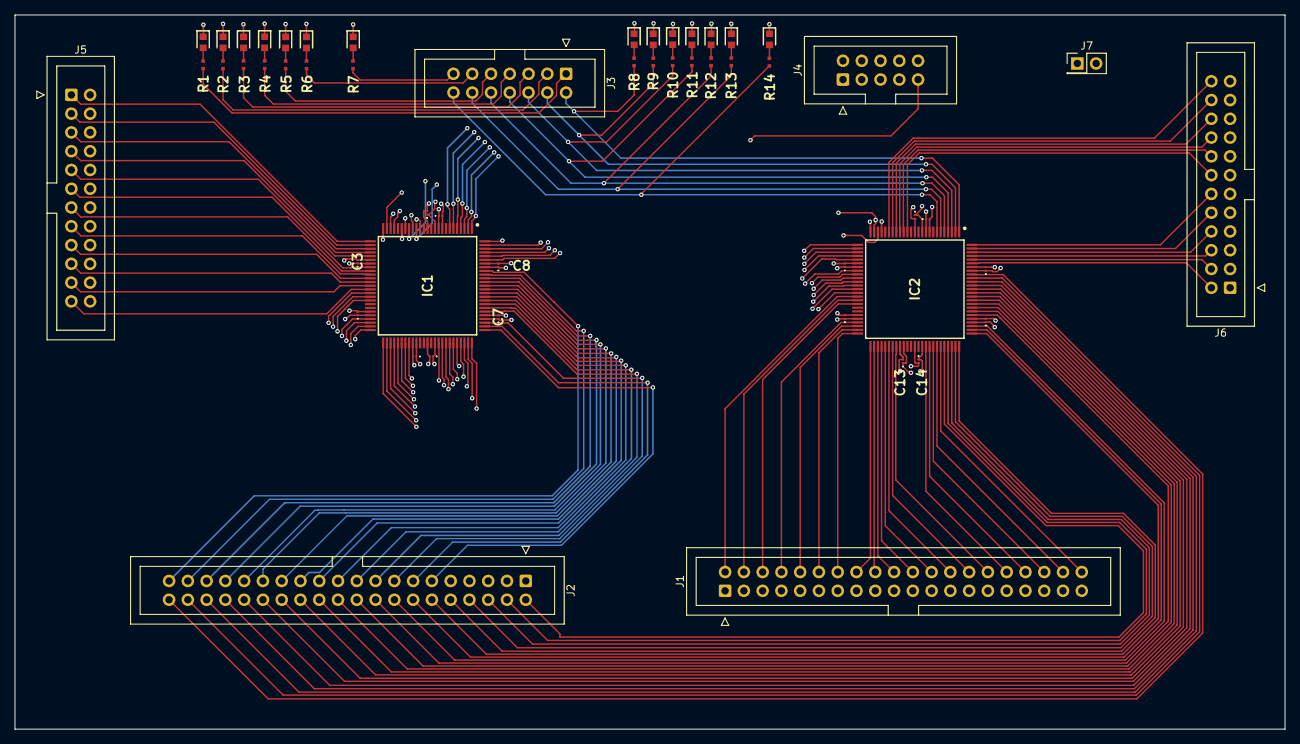
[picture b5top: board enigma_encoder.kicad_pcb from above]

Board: 6 copper layers, 171.8 x 96.6 mm, 53 parts (0 on the bottom side), 163 nets.
